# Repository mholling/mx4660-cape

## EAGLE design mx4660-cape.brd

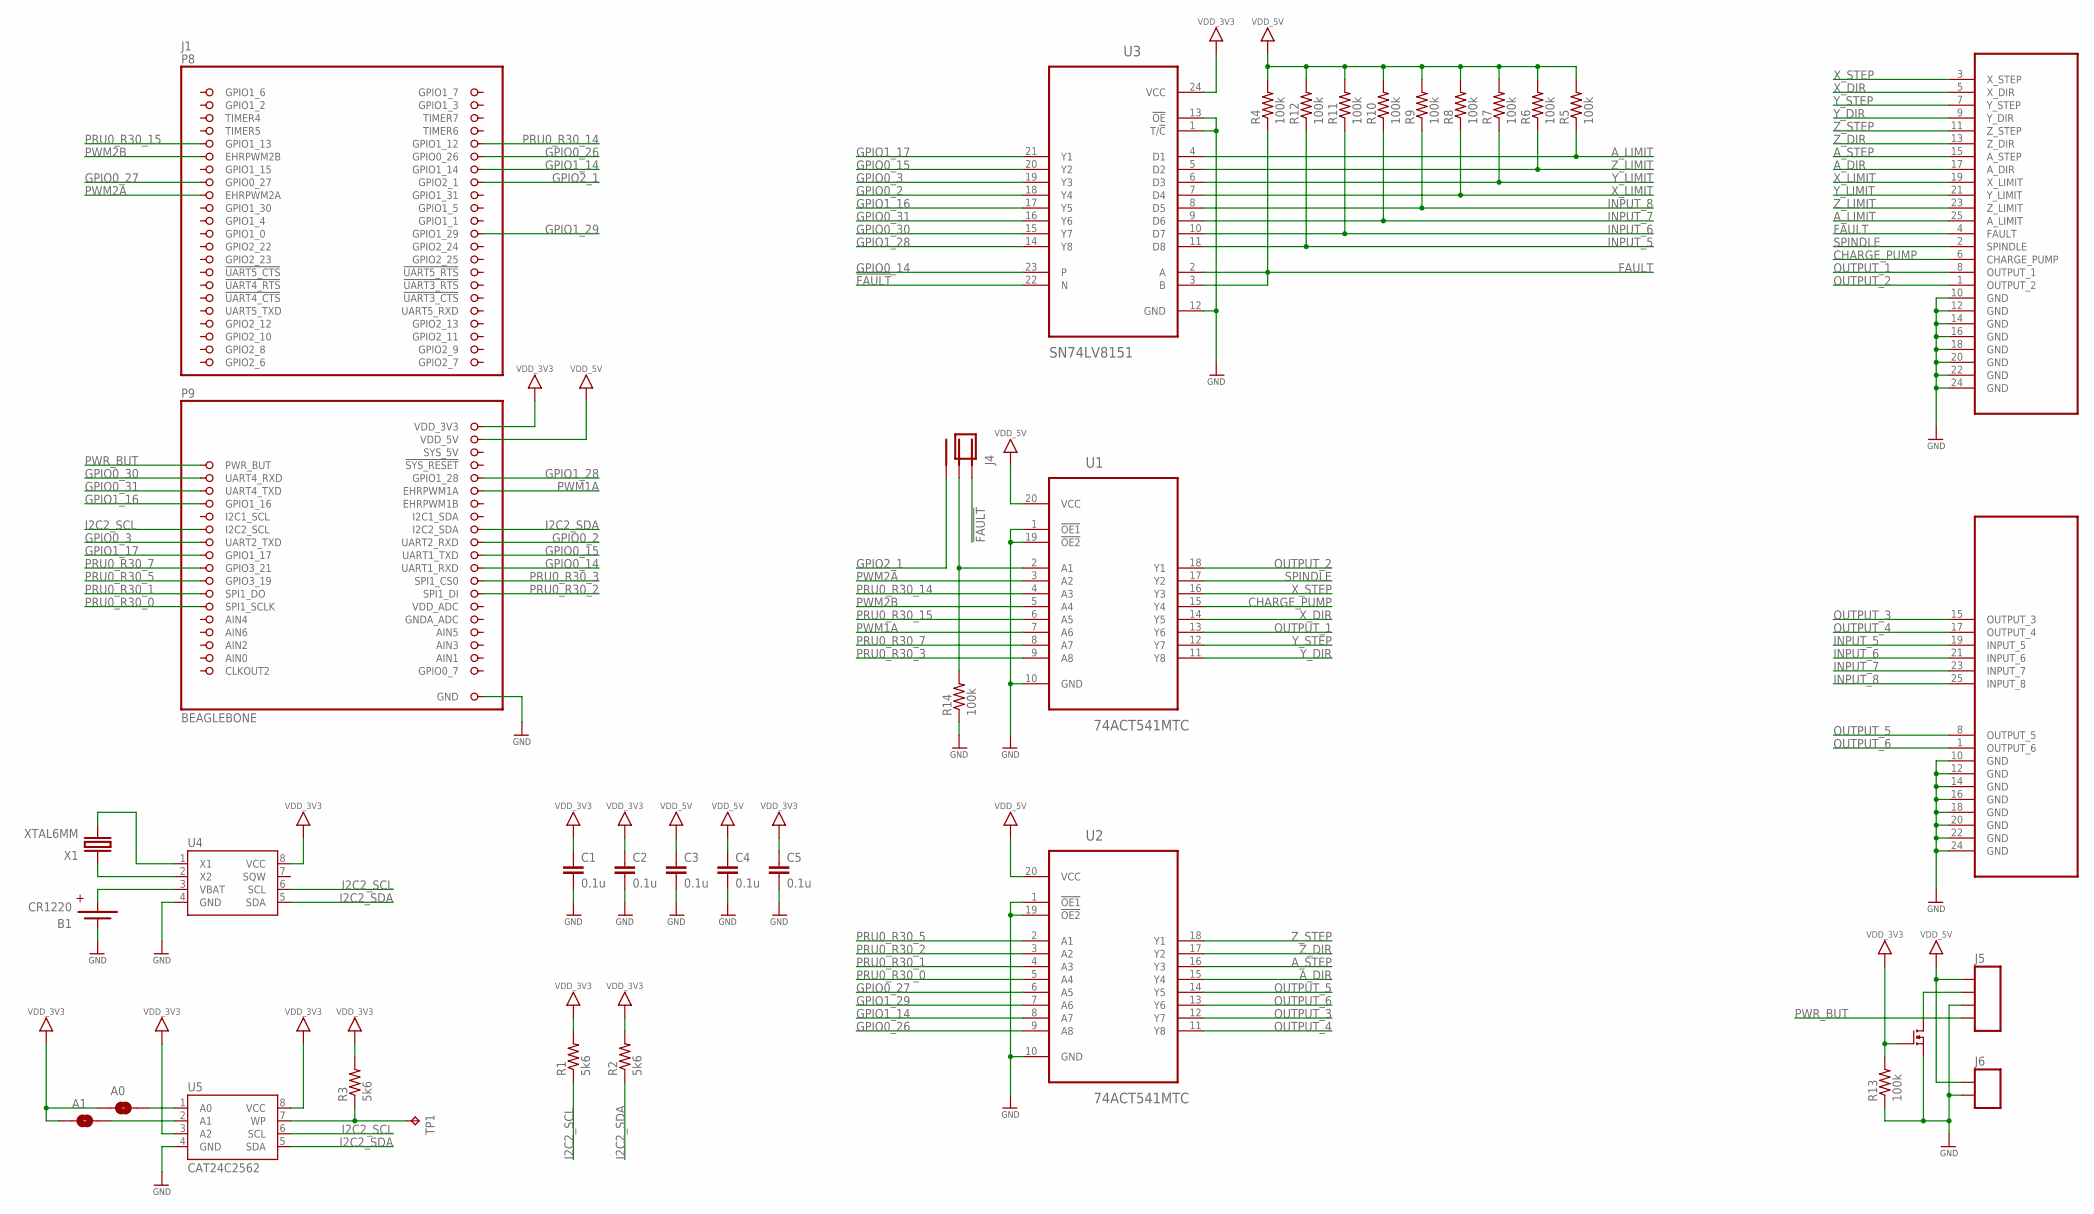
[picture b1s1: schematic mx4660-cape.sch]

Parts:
A0, A1: SOLDERJUMPERNO; SJ_2S-NO
B1: CR1220; 3000
C1, C2, C3, C4, C5: 0.1u; 0805
J1: BEAGLEBONE
J2: MX4660-CN1; HEADER-26-RA
J3: MX4660-CN10; HEADER-26-RA
J4: JUMPER-3P
J5: TERMINAL-4P3.5MM; TERMINAL-4P-3.5MM
J6: TERMINAL-2P-3.5MM
R1, R2, R3: 5k6; 0805
R4, R5, R6, R7, R8, R9, R10, R11, R12, R13, R14: 100k; 0805
TP1: TPB1,27; B1,27
U1, U2: 74ACT541MTC; TSSOP-20
U3: SN74LV8151; TSSOP-24
U4: RTC-DS; SOIC-8-2
U5: CAT24C2562; SOIC-8-2
U$36: BSS138; SOT23
X1: XTAL6MM; XTAL-6MM

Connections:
!FAULT: J4.1, U3.22 (N)
A0: A0.2, U5.1 (A0)
A1: A1.2, U5.2 (A1)
AIN0: J1.85 (AIN0)
A_DIR: J2.17 (A_DIR), U2.15 (Y4)
A_LIMIT: J2.25 (A_LIMIT), R5.1, U3.4 (D1)
A_STEP: J2.15 (A_STEP), U2.16 (Y3)
CHARGE_PUMP: J2.6 (CHARGE_PUMP), U1.15 (Y4)
FAULT: J2.4 (FAULT), R4.1, U3.2 (A), U3.3 (B)
GND: B1.NEGATIVE, C1.2, C2.2, C3.2, C4.2, C5.2, J1.1 (GND), J1.2 (GND), J1.47 (GND), J1.48 (GND), J1.89 (GND), J1.90 (GND), J1.91 (GND), J1.92 (GND), J2.10 (GND), J2.12 (GND), J2.14 (GND), J2.16 (GND), J2.18 (GND), J2.20 (GND), J2.22 (GND), J2.24 (GND), J3.10 (GND), J3.12 (GND), J3.14 (GND), J3.16 (GND), J3.18 (GND), J3.20 (GND), J3.22 (GND), J3.24 (GND), J5.P$2, J6.P$1, R13.1, R14.1, U1.1 (!OE1), U1.10 (GND), U1.19 (!OE2), U2.1 (!OE1), U2.10 (GND), U2.19 (!OE2), U3.1 (T/!C), U3.12 (GND), U3.13 (!OE), U4.4 (GND), U5.4 (GND), U$36.P$2
GPIO0_2: J1.68 (UART2_RXD), U3.18 (Y4)
GPIO0_3: J1.67 (UART2_TXD), U3.19 (Y3)
GPIO0_14: J1.72 (UART1_RXD), U3.23
GPIO0_15: J1.70 (UART1_TXD), U3.20 (Y2)
GPIO0_26: J1.14 (GPIO0_26), U2.9 (A8)
GPIO0_27: J1.17 (GPIO0_27), U2.6 (A5)
GPIO0_30: J1.57 (UART4_RXD), U3.15 (Y7)
GPIO0_31: J1.59 (UART4_TXD), U3.16 (Y6)
GPIO1_14: J1.16 (GPIO1_14), U2.8 (A7)
GPIO1_16: J1.61 (GPIO1_16), U3.17 (Y5)
GPIO1_17: J1.69 (GPIO1_17), U3.21 (Y1)
GPIO1_28: J1.58 (GPIO1_28), U3.14 (Y8)
GPIO1_29: J1.26 (GPIO1_29), U2.7 (A6)
GPIO2_1: J1.18 (GPIO2_1), J4.3
I2C2_SCL: J1.65 (I2C2_SCL), R1.1, U4.6 (SCL), U5.6 (SCL)
I2C2_SDA: J1.66 (I2C2_SDA), R2.1, U4.5 (SDA), U5.5 (SDA)
INPUT_5: J3.19 (INPUT_5), R12.1, U3.11 (D8)
INPUT_6: J3.21 (INPUT_6), R11.1, U3.10 (D7)
INPUT_7: J3.23 (INPUT_7), R10.1, U3.9 (D6)
INPUT_8: J3.25 (INPUT_8), R9.1, U3.8 (D5)
LED: J5.P$3, U$36.P$3
unnamed: J4.2, R14.2, U1.2 (A1)
unnamed: U4.2 (X2), X1.1
unnamed: U4.1 (X1), X1.2
OUTPUT_1: J2.8 (OUTPUT_1), U1.13 (Y6)
OUTPUT_2: J2.1 (OUTPUT_2), U1.18 (Y1)
OUTPUT_3: J3.15 (OUTPUT_3), U2.12 (Y7)
OUTPUT_4: J3.17 (OUTPUT_4), U2.11 (Y8)
OUTPUT_5: J3.8 (OUTPUT_5), U2.14 (Y5)
OUTPUT_6: J3.1 (OUTPUT_6), U2.13 (Y6)
PRU0_R30_0: J1.77 (SPI1_SCLK), U2.5 (A4)
PRU0_R30_1: J1.75 (SPI1_DO), U2.4 (A3)
PRU0_R30_2: J1.76 (SPI1_DI), U2.3 (A2)
PRU0_R30_3: J1.74 (SPI1_CS0), U1.9 (A8)
PRU0_R30_5: J1.73 (GPIO3_19), U2.2 (A1)
PRU0_R30_7: J1.71 (GPIO3_21), U1.8 (A7)
PRU0_R30_14: J1.12 (GPIO1_12), U1.4 (A3)
PRU0_R30_15: J1.11 (GPIO1_13), U1.6 (A5)
PWM1A: J1.60 (EHRPWM1A), U1.7 (A6)
PWM2A: J1.19 (EHRPWM2A), U1.3 (A2)
PWM2B: J1.13 (EHRPWM2B), U1.5 (A4)
PWR_BUT: J1.55 (PWR_BUT), J5.P$1
SPINDLE: J2.2 (SPINDLE), U1.17 (Y2)
VBAT: B1.POSITIVE2 (POSITIVE), U4.3 (VBAT)
VDD_3V3: A0.1, A1.1, C1.1, C2.1, C5.1, J1.49 (VDD_3V3), J1.50 (VDD_3V3), R1.2, R2.2, R3.2, R13.2, U3.24 (VCC), U4.8 (VCC), U5.3 (A2), U5.8 (VCC), U$36.P$1
VDD_5V: C3.1, C4.1, J1.51 (VDD_5V), J1.52 (VDD_5V), J5.P$4, J6.P$2, R4.2, R5.2, R6.2, R7.2, R8.2, R9.2, R10.2, R11.2, R12.2, U1.20 (VCC), U2.20 (VCC)
WP: R3.1, TP1.TP, U5.7 (WP)
X_DIR: J2.5 (X_DIR), U1.14 (Y5)
X_LIMIT: J2.19 (X_LIMIT), R8.1, U3.7 (D4)
X_STEP: J2.3 (X_STEP), U1.16 (Y3)
Y_DIR: J2.9 (Y_DIR), U1.11 (Y8)
Y_LIMIT: J2.21 (Y_LIMIT), R7.1, U3.6 (D3)
Y_STEP: J2.7 (Y_STEP), U1.12 (Y7)
Z_DIR: J2.13 (Z_DIR), U2.17 (Y2)
Z_LIMIT: J2.23 (Z_LIMIT), R6.1, U3.5 (D2)
Z_STEP: J2.11 (Z_STEP), U2.18 (Y1)

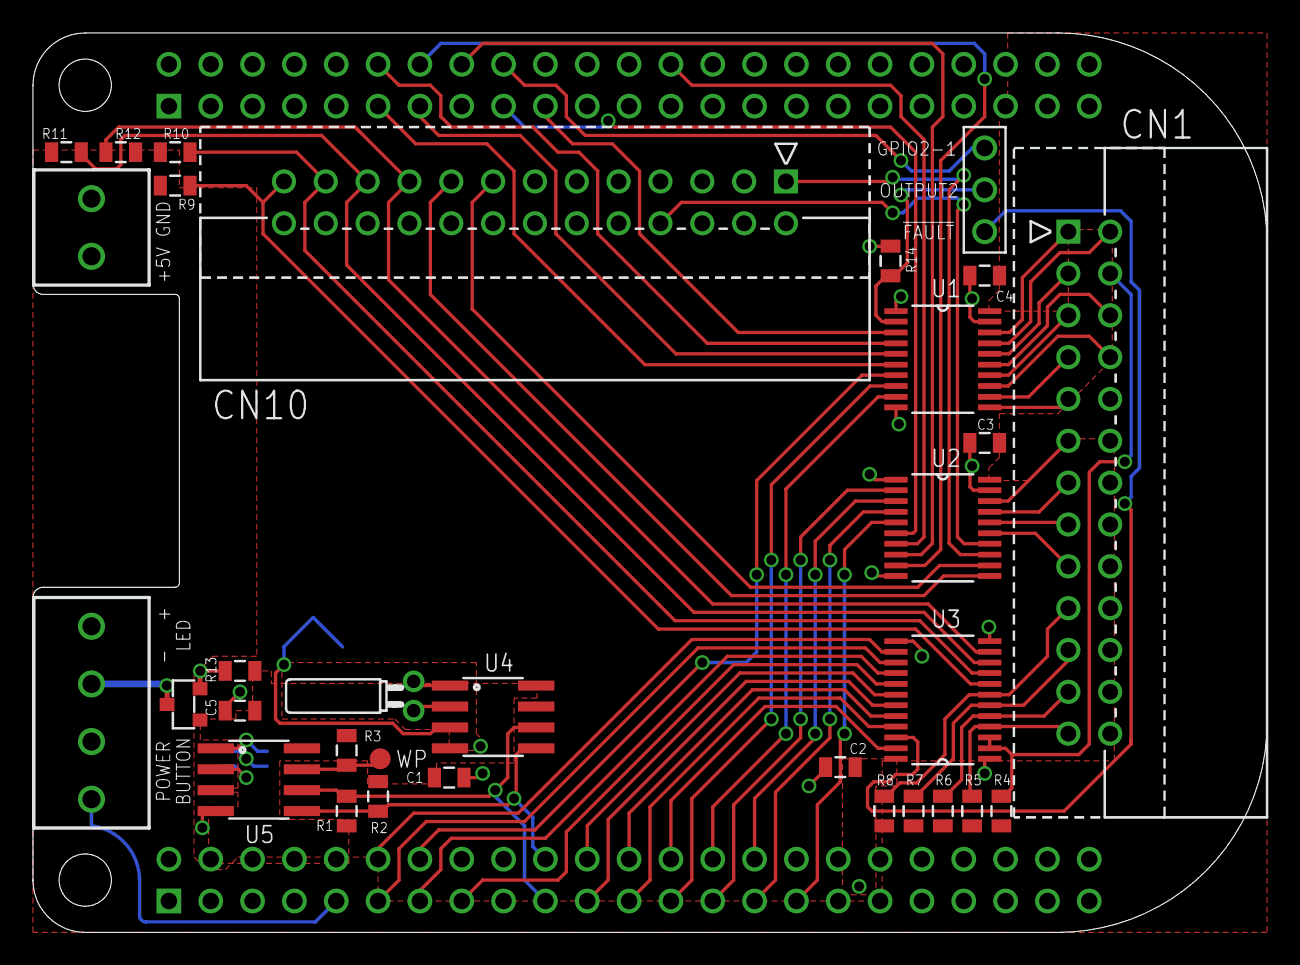
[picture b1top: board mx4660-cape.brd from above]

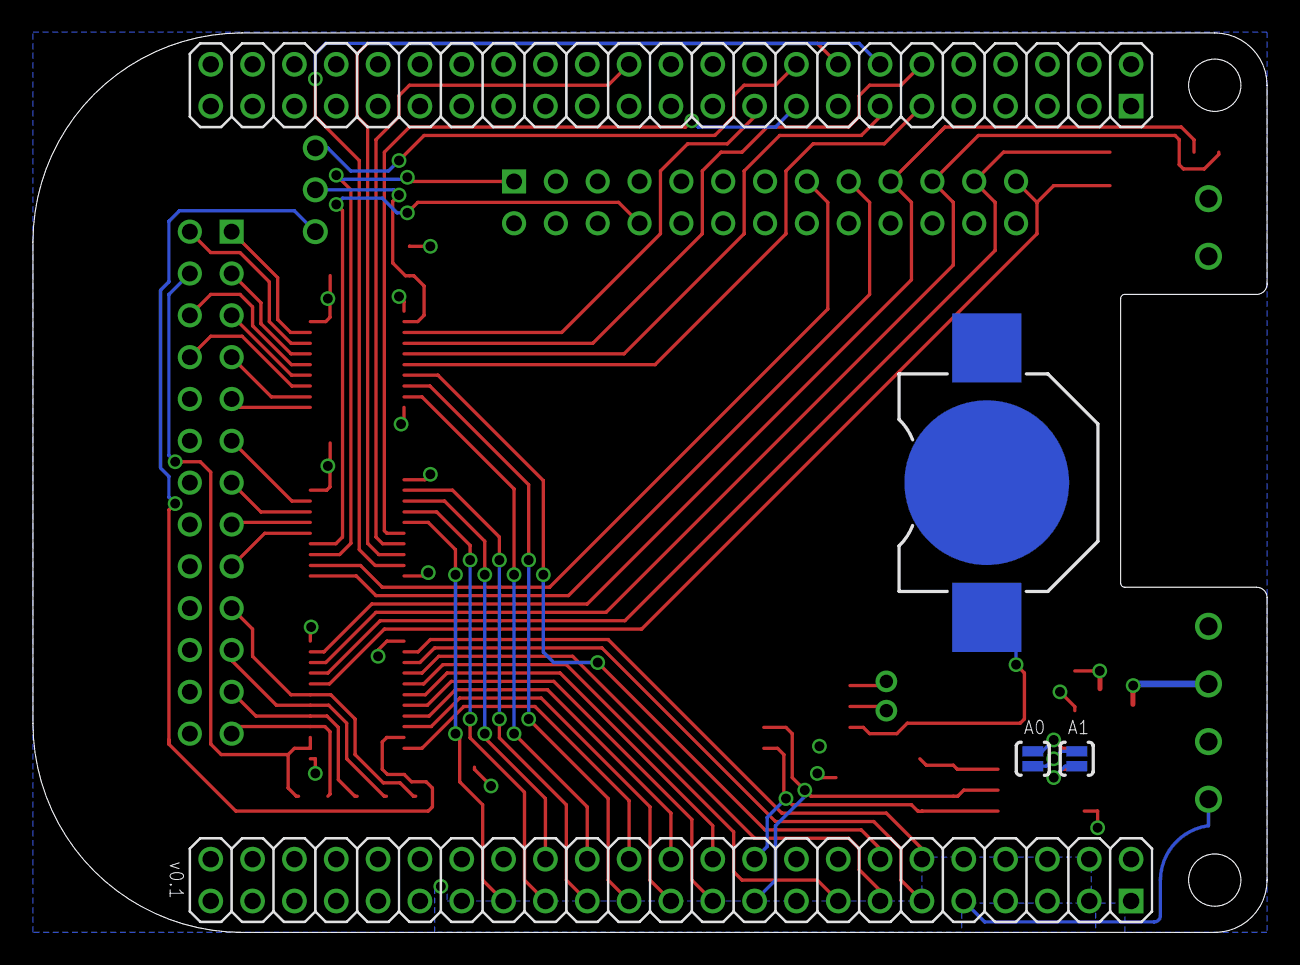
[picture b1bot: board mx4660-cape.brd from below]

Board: 2 copper layers, 74.9 x 54.6 mm, 36 parts (3 on the bottom side), 65 nets.

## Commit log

2016-04-27 initial commit v0.1
